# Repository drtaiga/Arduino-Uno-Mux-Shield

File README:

This repository contains all of the information required to produce an 8x1 multiplexer shield for the Arduino Uno. The shield features two sets of heavy duty screw terminals for coupling sensors to the Arduino. It is assumed that each sensor has three leads: one for Power (5V), one for a ground connection, and one for a return signal (0-5V). The shield is fully compatible with the Arduino Uno datalogger shield sold by Adafruit Industries, Inc. A full system (Arduino + datalogger + multiplexer shield) easily records input from up to 8 external sensors.   

UnoMuxShieldV1.0.brd -- the EAGLE printed circuit board layout

UnoMuxShieldV1.0.sch -- the EAGLE schematic for the circuit board

UnoMuxShieldV1.0_gerb.zip -- a zip file containing the Gerber files for the PCB. The files follow the format required by the PCB production house OSH Park (www.oshpark.com). If you upload the zip file to their web site, then they should be able to produce a PCB without a hitch.

UnoMuxShieldV1.0_png.zip -- a zip file containing images (.png format) of the board outline, silks, masks, and drills, etc. The files aren't necessary for production. However, you can view them in a standard image viewer to get a sense of what the final product will look like.  

ArduinoMuxParts.pdf -- a pdf file containing a list of of the parts required for executing the project. It also contains a list of selected vendors and vendor part numbers, which should make it easier for you to complete the project.

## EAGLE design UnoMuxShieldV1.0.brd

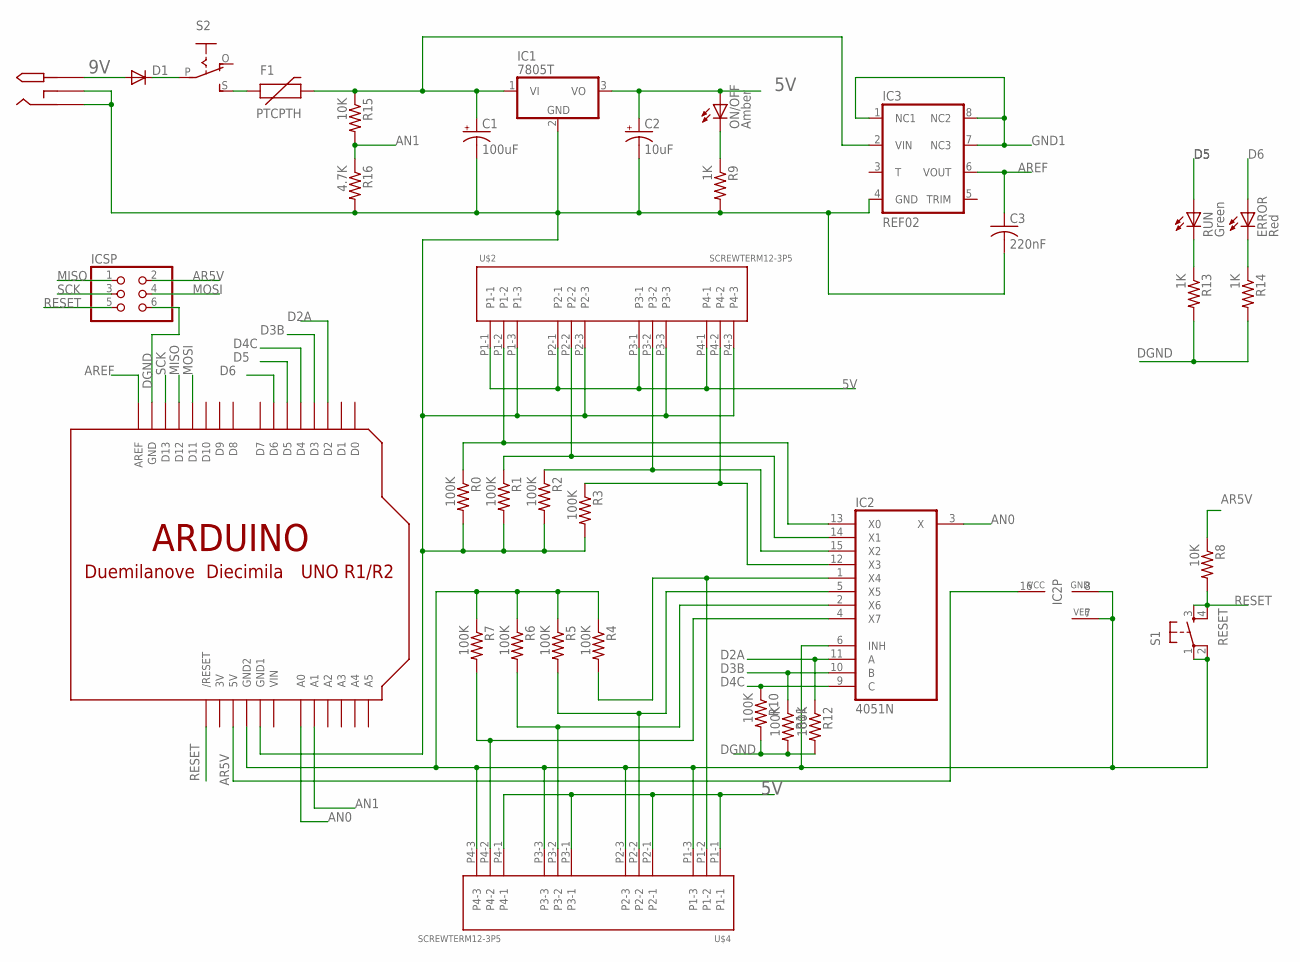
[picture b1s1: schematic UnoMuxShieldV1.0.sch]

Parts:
C1: 100uF; E2,5-6E
C2: 10uF; E1,8-4
C3: 220nF; C050-024X044
D1: DIODEPTH; DIODE-1N4001
ERROR: Red; LED3MM
F1: PTCPTH; PTC
IC1: 7805T; TO220H
IC2: 4051N; DIL16
IC3: REF02; DIL08
ICSP: PINHD-2X3; 2X03
ON/OFF: Amber; LED3MM
R0, R1, R2, R3, R4, R5, R6, R7, R10, R11, R12: 100K; 0207/10
R8, R15: 10K; 0207/10
R9, R13, R14: 1K; 0207/10
R16: 4.7K; 0207/10
RUN: Green; LED3MM
S1: RESET; TACTILE-PTH
S2: EG1218S; EG1218
U$1: ARDUINO-NOHOLE
U$2, U$4: SCREWTERM12-3P5; SCREWTERM3P5
U$5: PJ-102-A

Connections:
3V: U$1.3V
5V: C2.+, IC1.3 (VO), ON/OFF.A, U$2.P1-1, U$2.P2-1, U$2.P3-1, U$2.P4-1, U$4.P1-1, U$4.P2-1, U$4.P3-1, U$4.P4-1
9V: D1.A, U$5.P$1_TIP (TIP)
AN0: IC2.3 (X), U$1.A0
AN1: R15.2, R16.1, U$1.A1
AR5V: IC2.16 (VCC), ICSP.2, R8.1, U$1.5V
AREF: C3.1, IC3.6 (VOUT), U$1.AREF
D2A: IC2.11 (A), R12.1, U$1.D2
D3B: IC2.10 (B), R11.1, U$1.D3
D4C: IC2.9 (C), R10.1, U$1.D4
D5: RUN.A, U$1.D5
D6: ERROR.A, U$1.D6
DGND: ICSP.6, R10.2, R11.2, R12.2, R13.2, R14.2, U$1.GND
GND1: IC3.1 (NC1), IC3.7 (NC3), IC3.8 (NC2)
MISO: ICSP.1, U$1.D12
MOSI: ICSP.4, U$1.D11
unnamed: IC2.13 (X0), R0.1, U$2.P1-2
unnamed: D1.C, S2.P
unnamed: F1.P$1 (1), S2.S
unnamed: C1.-, C2.-, C3.2, IC1.2 (GND), IC3.4 (GND), R0.2, R1.2, R2.2, R3.2, R9.2, R16.2, U$1.GND1, U$2.P1-3, U$2.P2-3, U$2.P3-3, U$2.P4-3, U$5.P$2_SLEEVE (SLEEVE), U$5.P$3_SHUNT (SHUNT)
unnamed: IC2.12 (X3), R3.1, U$2.P4-2
unnamed: ON/OFF.K (C), R9.1
unnamed: IC2.6 (INH), IC2.7 (VEE), IC2.8 (GND), R4.1, R5.1, R6.1, R7.1, S1.1, S1.2, U$1.GND2, U$4.P1-3, U$4.P2-3, U$4.P3-3, U$4.P4-3
unnamed: IC2.1 (X4), R4.2, U$4.P1-2
unnamed: IC2.5 (X5), R5.2, U$4.P2-2
unnamed: IC2.2 (X6), R6.2, U$4.P3-2
unnamed: IC2.4 (X7), R7.2, U$4.P4-2
unnamed: IC2.15 (X2), R2.1, U$2.P3-2
unnamed: R13.1, RUN.K (C)
unnamed: ERROR.K (C), R14.1
unnamed: C1.+, F1.P$2 (2), IC1.1 (VI), IC3.2 (VIN), R15.1
unnamed: IC2.14 (X1), R1.1, U$2.P2-2
RESET: ICSP.5, R8.2, S1.3, S1.4, U$1.RESET (/RESET)
SCK: ICSP.3, U$1.D13
TRIM: IC3.5 (TRIM)
VIN: U$1.VIN

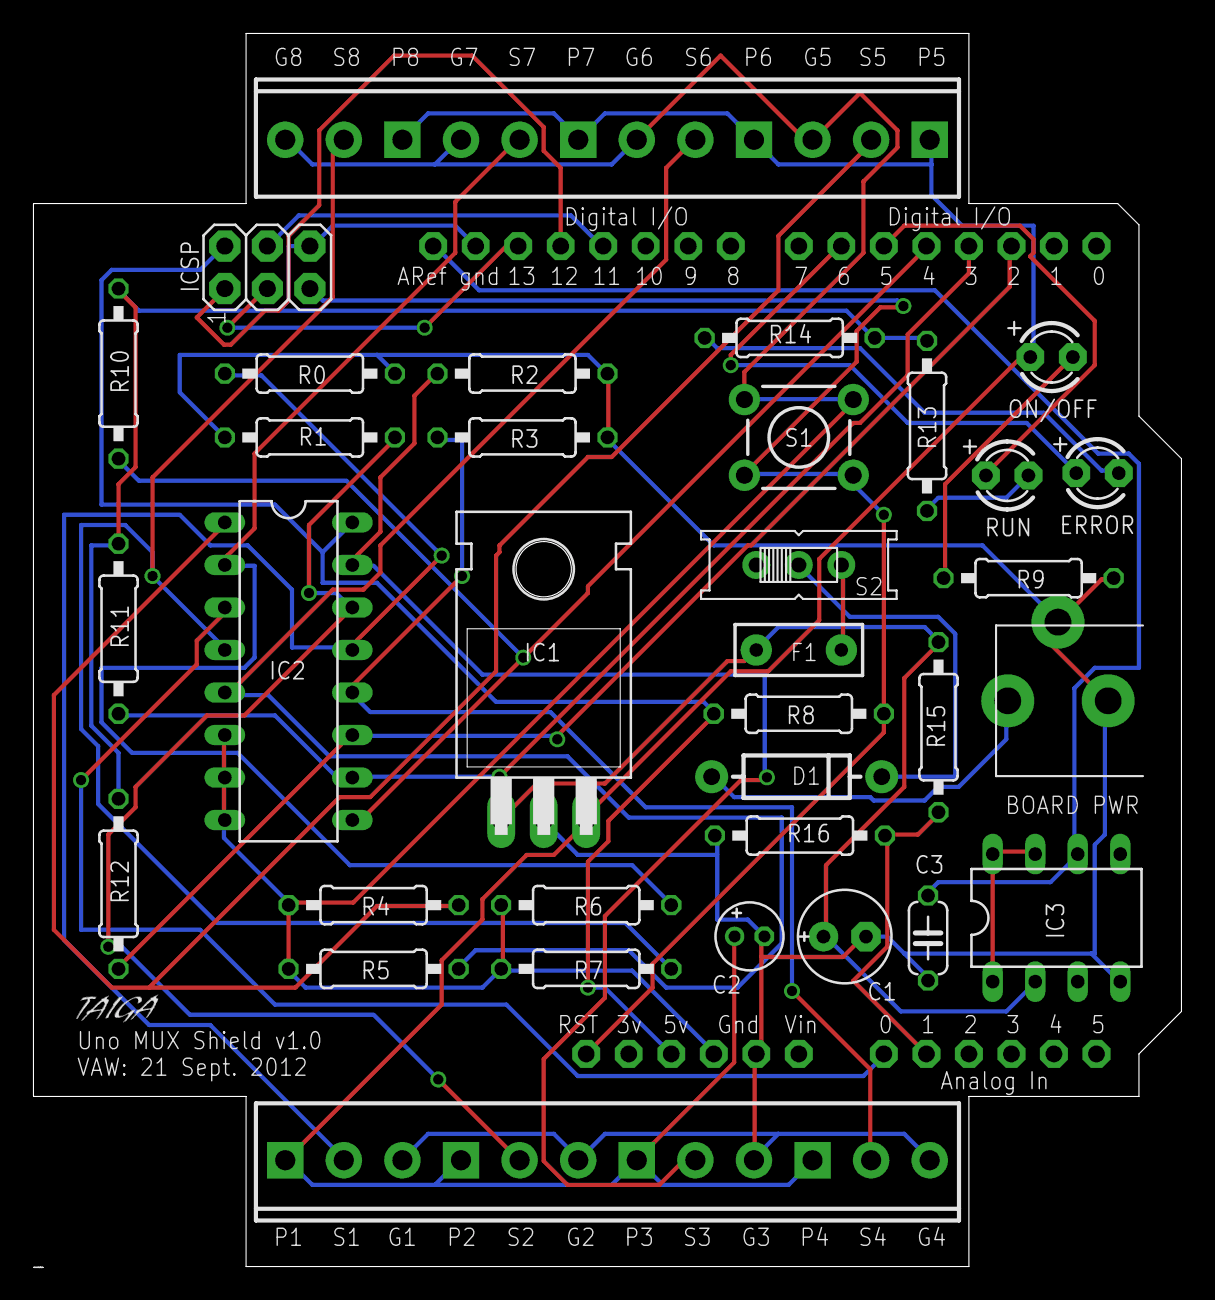
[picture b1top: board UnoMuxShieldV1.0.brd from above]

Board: 2 copper layers, 68.6 x 73.7 mm, 35 parts (0 on the bottom side), 33 nets.

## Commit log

2012-09-24 Initial Version
2012-09-24 Test
2013-01-18 Modified the README file and added a parts list file
2013-04-05 Updated parts list
    Slight update of the parts/vendor list.
2016-11-26 test
    test

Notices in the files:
parts and their libraries:
SparkFun-DiscreteSemi: Licensing: CC v3.0 Share-Alike You are welcome to use this library for commercial purposes.
VAW: Released under the Creative Commons
VAW: http://creativecommons.org/licenses/by-sa/3.0
